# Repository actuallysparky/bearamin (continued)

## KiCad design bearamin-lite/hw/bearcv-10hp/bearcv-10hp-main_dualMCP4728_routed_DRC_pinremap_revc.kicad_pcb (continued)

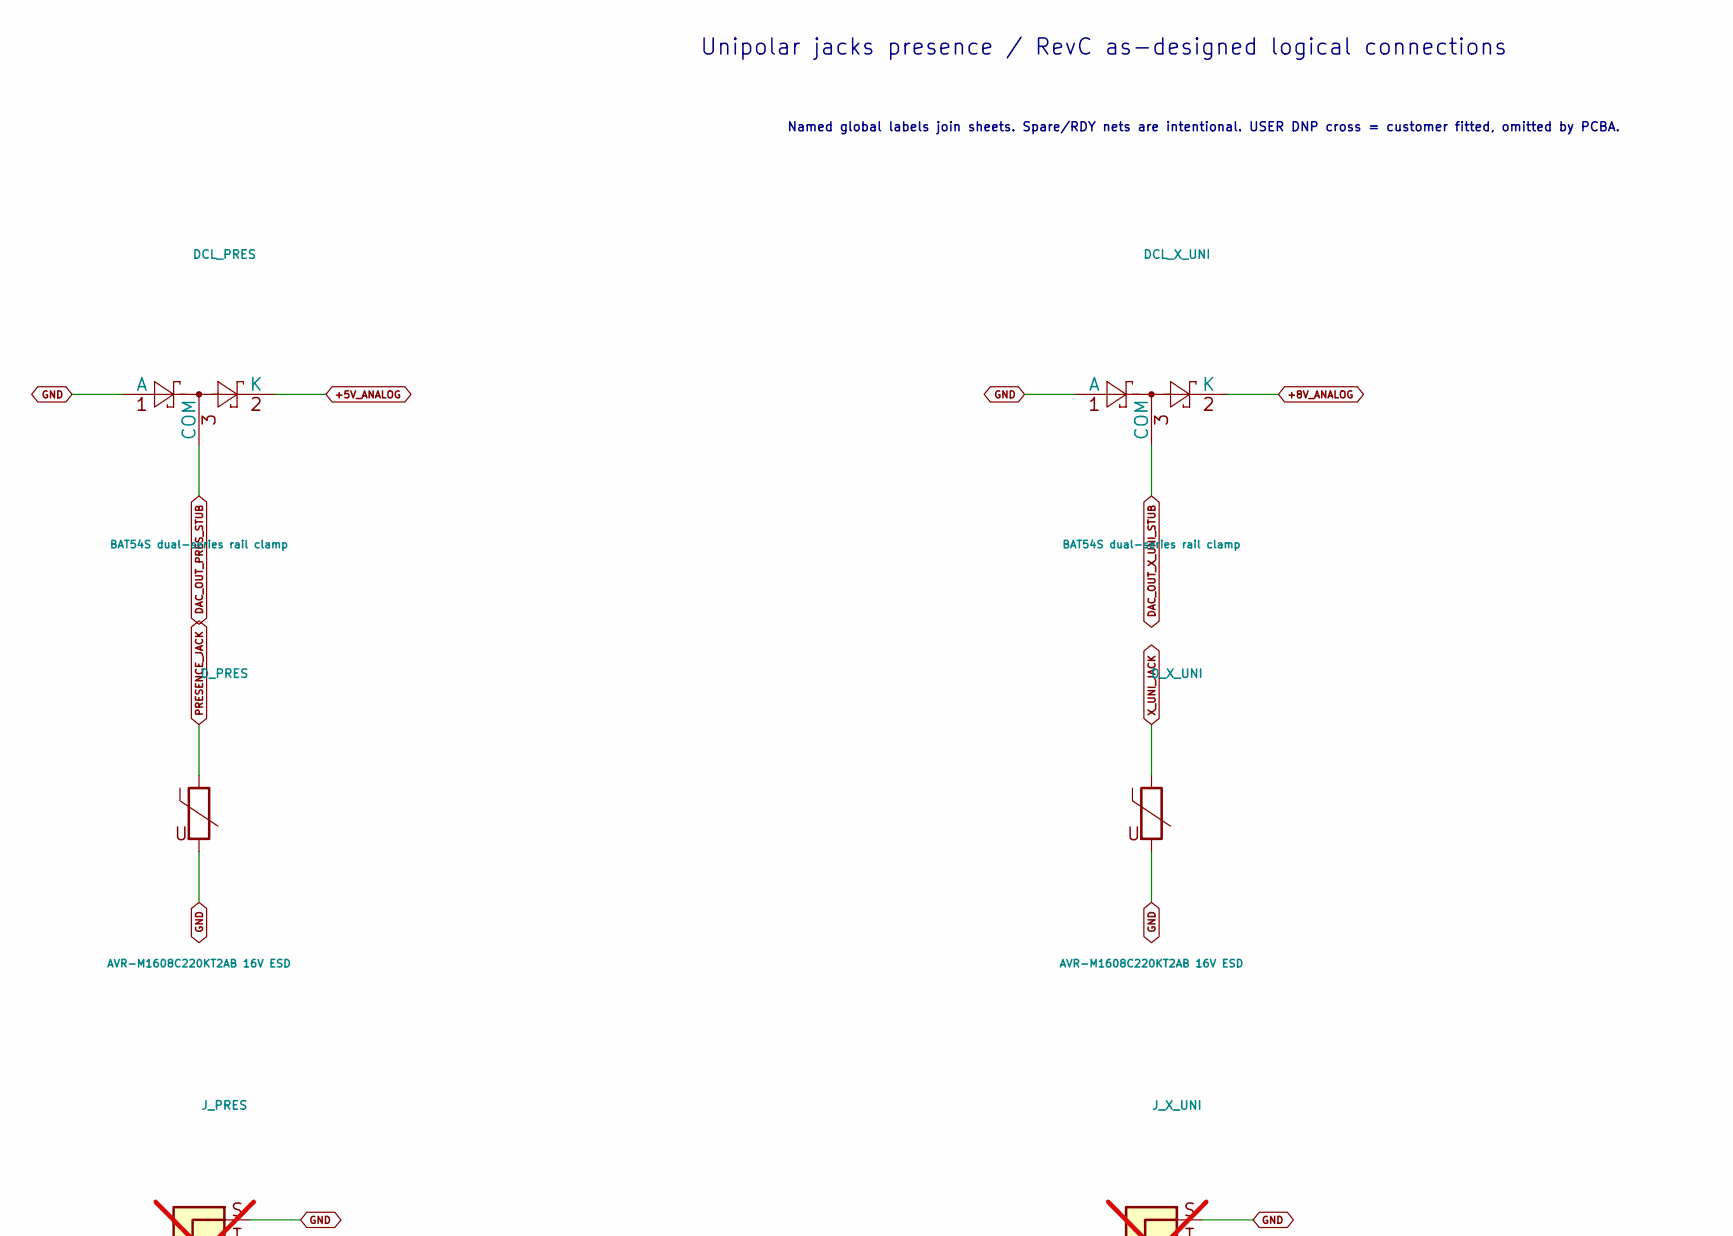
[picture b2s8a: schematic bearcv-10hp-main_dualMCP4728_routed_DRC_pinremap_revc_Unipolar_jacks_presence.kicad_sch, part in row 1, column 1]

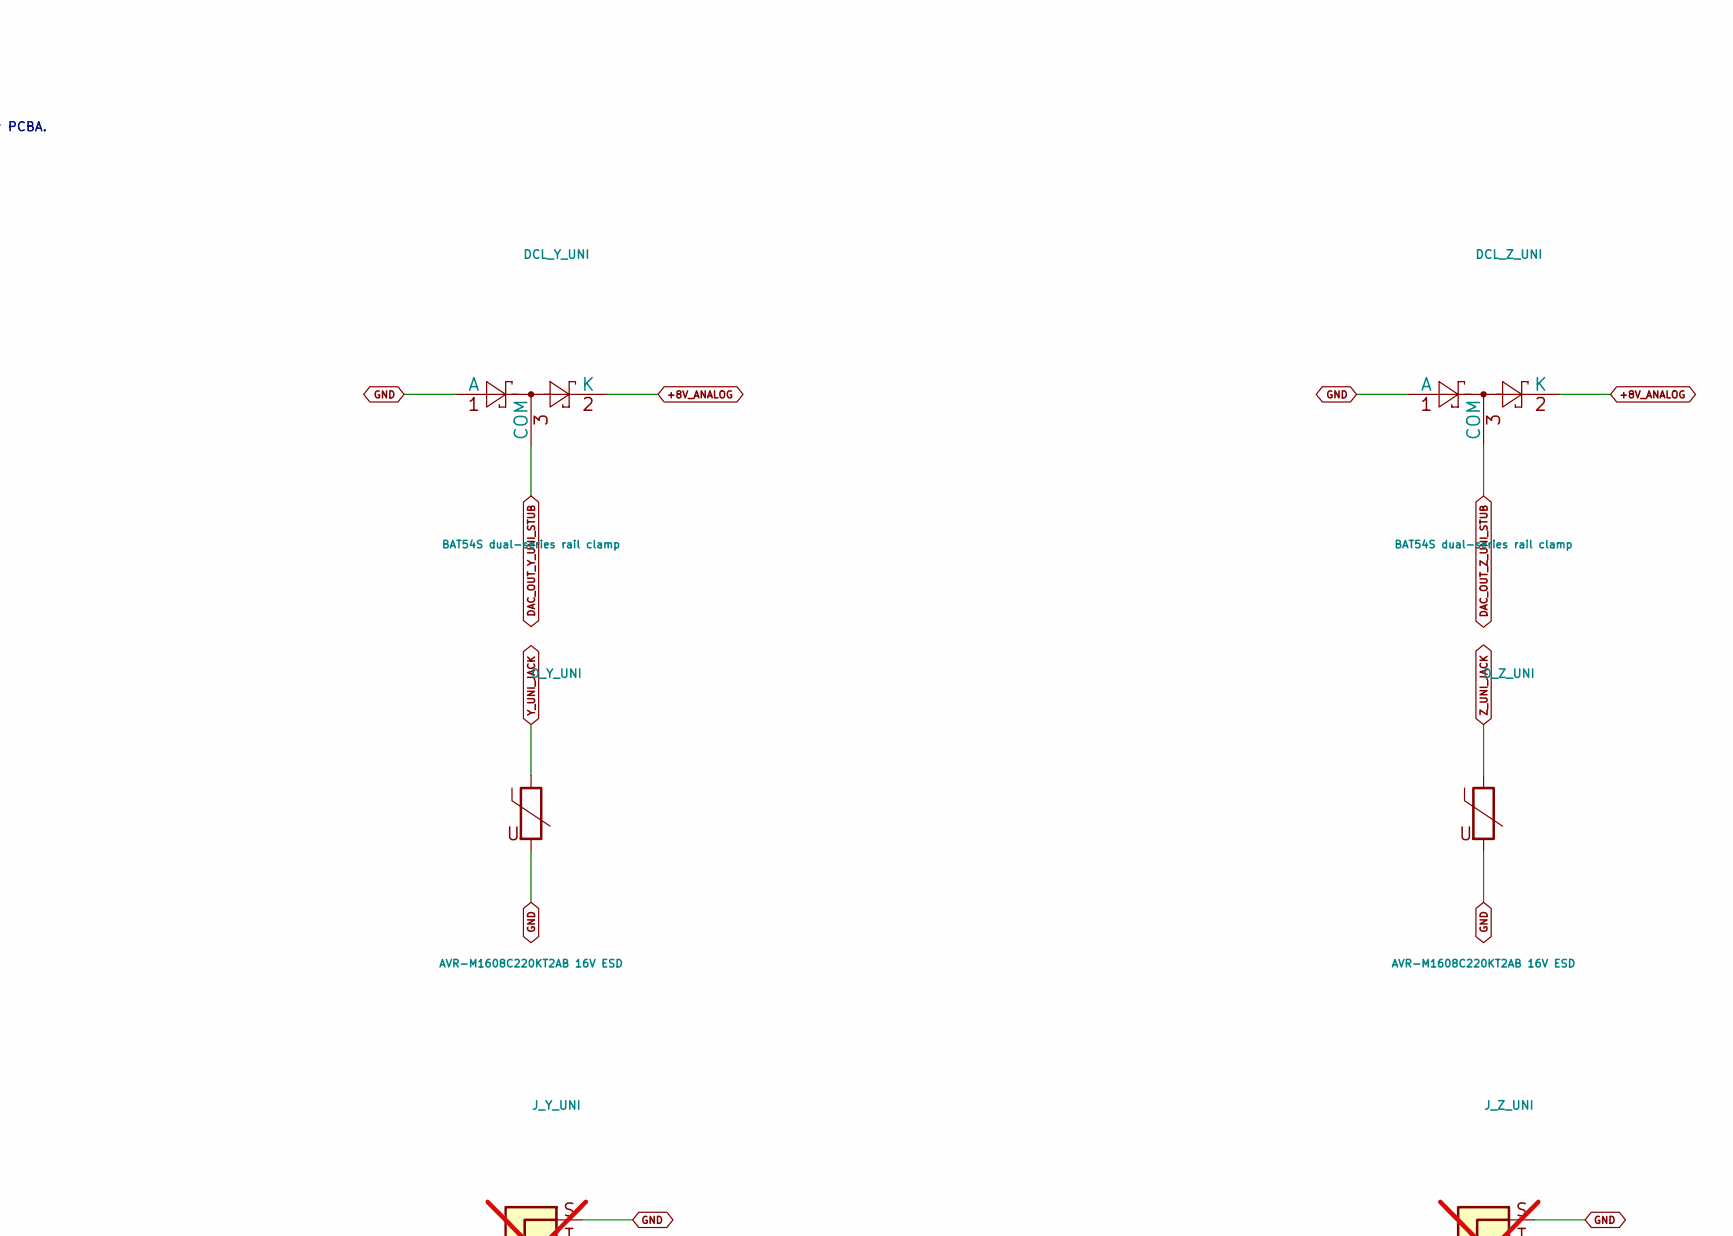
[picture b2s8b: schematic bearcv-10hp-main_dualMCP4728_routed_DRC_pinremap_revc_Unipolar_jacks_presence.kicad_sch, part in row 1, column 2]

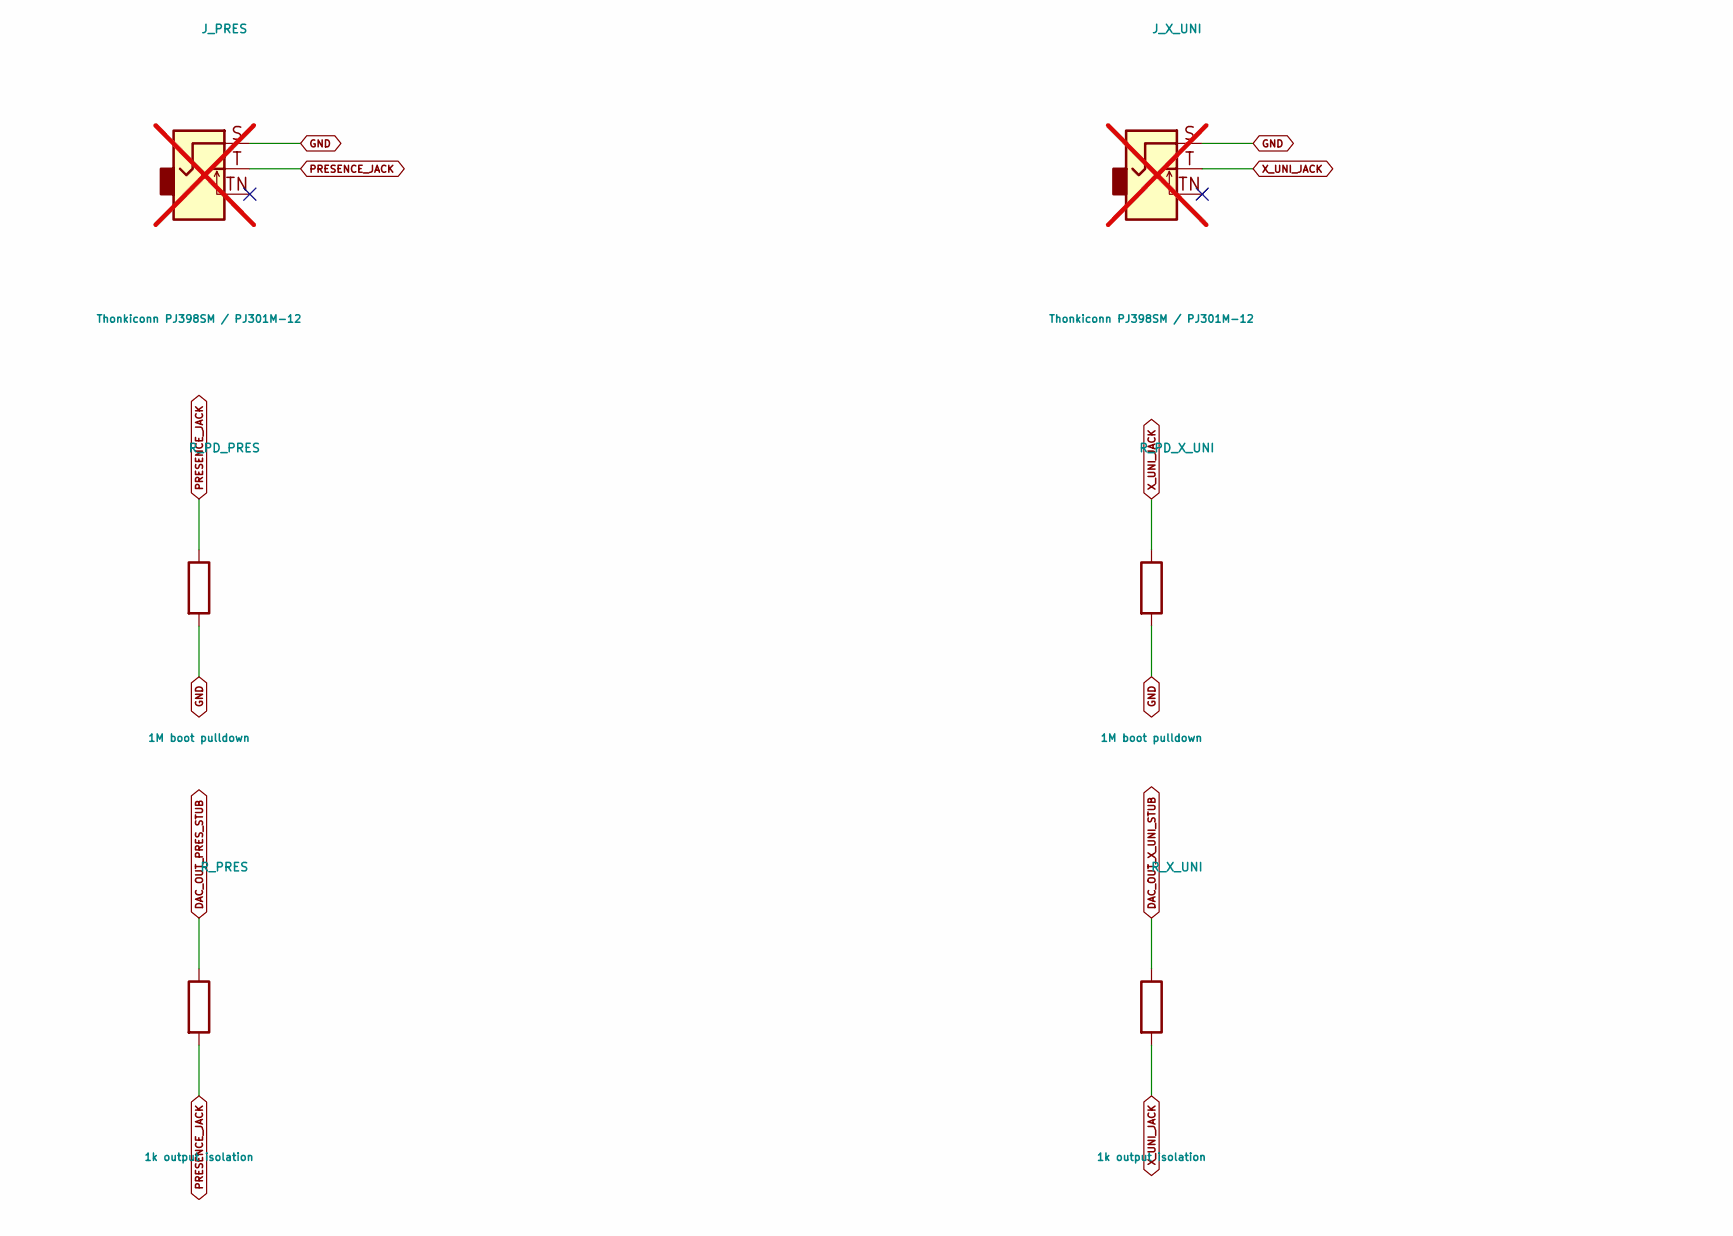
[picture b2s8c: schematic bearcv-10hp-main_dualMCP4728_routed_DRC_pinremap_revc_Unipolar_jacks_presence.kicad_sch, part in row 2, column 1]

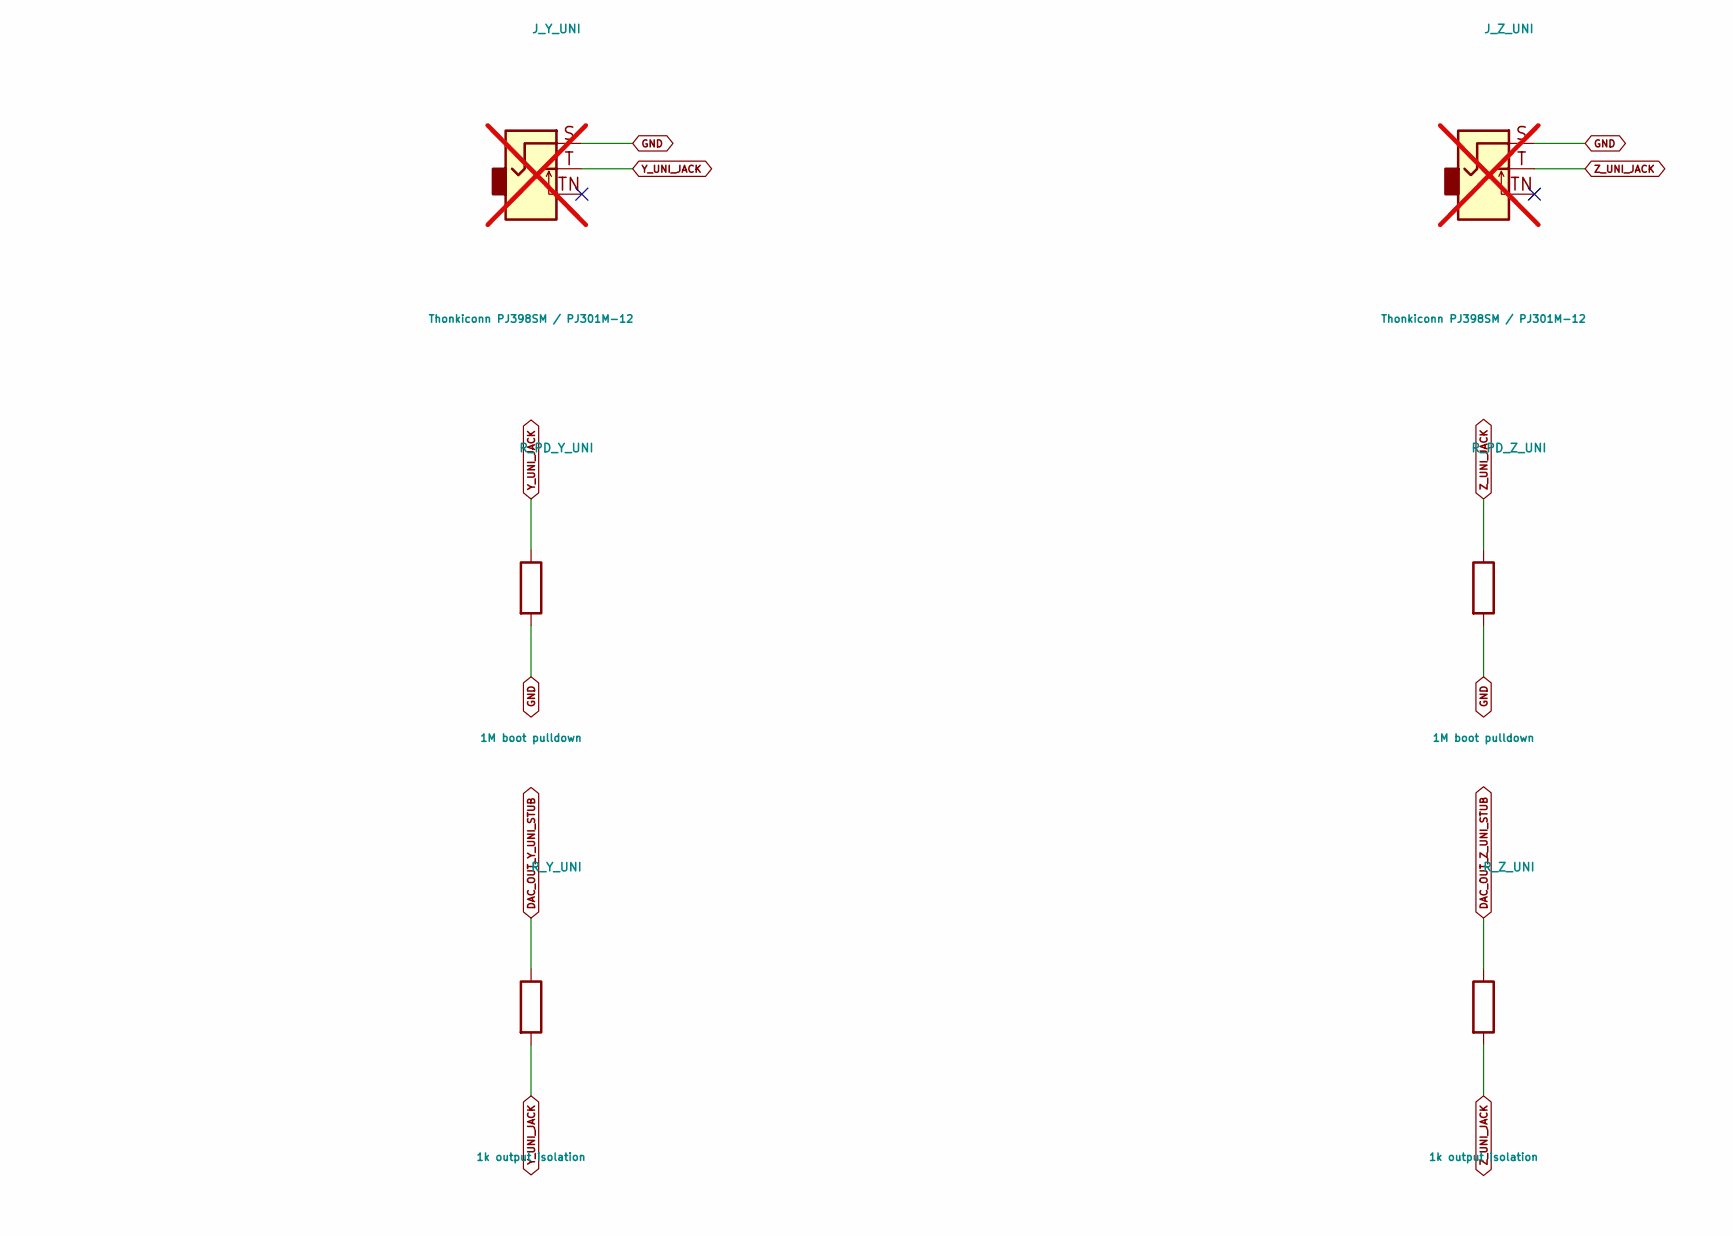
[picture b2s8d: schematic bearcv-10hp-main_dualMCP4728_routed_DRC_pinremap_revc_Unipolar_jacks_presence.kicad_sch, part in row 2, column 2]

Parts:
DCL_PRES: BAT54S dual-series rail clamp; MPN BAT54S-7-F; JLCPCB Part C83574
DCL_X_UNI: BAT54S dual-series rail clamp; MPN BAT54S-7-F; JLCPCB Part C83574
DCL_Y_UNI: BAT54S dual-series rail clamp; MPN BAT54S-7-F; JLCPCB Part C83574
DCL_Z_UNI: BAT54S dual-series rail clamp; MPN BAT54S-7-F; JLCPCB Part C83574
D_PRES: AVR-M1608C220KT2AB 16V ESD; MPN AVR-M1608C220KT2AB; JLCPCB Library Extended
D_X_UNI: AVR-M1608C220KT2AB 16V ESD; MPN AVR-M1608C220KT2AB; JLCPCB Library Extended
D_Y_UNI: AVR-M1608C220KT2AB 16V ESD; MPN AVR-M1608C220KT2AB; JLCPCB Library Extended
D_Z_UNI: AVR-M1608C220KT2AB 16V ESD; MPN AVR-M1608C220KT2AB; JLCPCB Library Extended
J_PRES: Thonkiconn PJ398SM / PJ301M-12; Jack_3.5mm_QingPu_WQP-PJ398SM_Vertical_CircularHoles; MPN DNP; not fitted
J_X_UNI: Thonkiconn PJ398SM / PJ301M-12; Jack_3.5mm_QingPu_WQP-PJ398SM_Vertical_CircularHoles; MPN DNP; not fitted
J_Y_UNI: Thonkiconn PJ398SM / PJ301M-12; Jack_3.5mm_QingPu_WQP-PJ398SM_Vertical_CircularHoles; MPN DNP; not fitted
J_Z_UNI: Thonkiconn PJ398SM / PJ301M-12; Jack_3.5mm_QingPu_WQP-PJ398SM_Vertical_CircularHoles; MPN DNP; not fitted
R_PD_PRES: 1M boot pulldown; MPN 0603WAF1004T5E; JLCPCB Part C22935
R_PD_X_UNI: 1M boot pulldown; MPN 0603WAF1004T5E; JLCPCB Part C22935
R_PD_Y_UNI: 1M boot pulldown; MPN 0603WAF1004T5E; JLCPCB Part C22935
R_PD_Z_UNI: 1M boot pulldown; MPN 0603WAF1004T5E; JLCPCB Part C22935
R_PRES: 1k output isolation; MPN 0603WAF1001T5E; JLCPCB Part C21190
R_X_UNI: 1k output isolation; MPN 0603WAF1001T5E; JLCPCB Part C21190
R_Y_UNI: 1k output isolation; MPN 0603WAF1001T5E; JLCPCB Part C21190
R_Z_UNI: 1k output isolation; MPN 0603WAF1001T5E; JLCPCB Part C21190

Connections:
+5V_ANALOG: DCL_PRES.2 (K); also elsewhere on the board
+8V_ANALOG: DCL_X_UNI.2 (K), DCL_Y_UNI.2 (K), DCL_Z_UNI.2 (K); also elsewhere on the board
DAC_OUT_PRES_STUB: DCL_PRES.3 (COM), R_PRES.1; also elsewhere on the board
DAC_OUT_X_UNI_STUB: DCL_X_UNI.3 (COM), R_X_UNI.1; also elsewhere on the board
DAC_OUT_Y_UNI_STUB: DCL_Y_UNI.3 (COM), R_Y_UNI.1; also elsewhere on the board
DAC_OUT_Z_UNI_STUB: DCL_Z_UNI.3 (COM), R_Z_UNI.1; also elsewhere on the board
GND: DCL_PRES.1 (A), DCL_X_UNI.1 (A), DCL_Y_UNI.1 (A), DCL_Z_UNI.1 (A), D_PRES.2, D_X_UNI.2, D_Y_UNI.2, D_Z_UNI.2, J_PRES.S, J_X_UNI.S, J_Y_UNI.S, J_Z_UNI.S, R_PD_PRES.2, R_PD_X_UNI.2, R_PD_Y_UNI.2, R_PD_Z_UNI.2; also elsewhere on the board
PRESENCE_JACK: D_PRES.1, J_PRES.T, R_PD_PRES.1, R_PRES.2
X_UNI_JACK: D_X_UNI.1, J_X_UNI.T, R_PD_X_UNI.1, R_X_UNI.2
Y_UNI_JACK: D_Y_UNI.1, J_Y_UNI.T, R_PD_Y_UNI.1, R_Y_UNI.2
Z_UNI_JACK: D_Z_UNI.1, J_Z_UNI.T, R_PD_Z_UNI.1, R_Z_UNI.2

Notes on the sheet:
Unipolar jacks presence / RevC as-designed logical connections
Named global labels join sheets. Spare/RDY nets are intentional. USER DNP cross = customer fitted, omitted by PCBA.

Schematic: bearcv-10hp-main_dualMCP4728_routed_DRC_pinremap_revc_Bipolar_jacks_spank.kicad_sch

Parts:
DCL_SPANK: BAT54S dual-series rail clamp; MPN BAT54S-7-F; JLCPCB Part C83574
DCL_X_BI: BAT54S dual-series rail clamp; MPN BAT54S-7-F; JLCPCB Part C83574
DCL_Y_BI: BAT54S dual-series rail clamp; MPN BAT54S-7-F; JLCPCB Part C83574
DCL_Z_BI: BAT54S dual-series rail clamp; MPN BAT54S-7-F; JLCPCB Part C83574
D_SPANK: AVR-M1608C220KT2AB 16V ESD; MPN AVR-M1608C220KT2AB; JLCPCB Library Extended
D_X_BI: AVR-M1608C220KT2AB 16V ESD; MPN AVR-M1608C220KT2AB; JLCPCB Library Extended
D_Y_BI: AVR-M1608C220KT2AB 16V ESD; MPN AVR-M1608C220KT2AB; JLCPCB Library Extended
D_Z_BI: AVR-M1608C220KT2AB 16V ESD; MPN AVR-M1608C220KT2AB; JLCPCB Library Extended
J_SPANK: Thonkiconn PJ398SM / PJ301M-12; Jack_3.5mm_QingPu_WQP-PJ398SM_Vertical_CircularHoles; MPN DNP; not fitted
J_X_BI: Thonkiconn PJ398SM / PJ301M-12; Jack_3.5mm_QingPu_WQP-PJ398SM_Vertical_CircularHoles; MPN DNP; not fitted
J_Y_BI: Thonkiconn PJ398SM / PJ301M-12; Jack_3.5mm_QingPu_WQP-PJ398SM_Vertical_CircularHoles; MPN DNP; not fitted
J_Z_BI: Thonkiconn PJ398SM / PJ301M-12; Jack_3.5mm_QingPu_WQP-PJ398SM_Vertical_CircularHoles; MPN DNP; not fitted
R_PD_SPANK: 1M boot pulldown; MPN 0603WAF1004T5E; JLCPCB Part C22935
R_PD_X_BI: 1M boot pulldown; MPN 0603WAF1004T5E; JLCPCB Part C22935
R_PD_Y_BI: 1M boot pulldown; MPN 0603WAF1004T5E; JLCPCB Part C22935
R_PD_Z_BI: 1M boot pulldown; MPN 0603WAF1004T5E; JLCPCB Part C22935
R_SPANK: 1k output isolation; MPN 0603WAF1001T5E; JLCPCB Part C21190
R_X_BI: 1k output isolation; MPN 0603WAF1001T5E; JLCPCB Part C21190
R_Y_BI: 1k output isolation; MPN 0603WAF1001T5E; JLCPCB Part C21190
R_Z_BI: 1k output isolation; MPN 0603WAF1001T5E; JLCPCB Part C21190

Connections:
+5V_ANALOG: DCL_SPANK.2 (K); also elsewhere on the board
+8V_ANALOG: DCL_X_BI.2 (K), DCL_Y_BI.2 (K), DCL_Z_BI.2 (K); also elsewhere on the board
-8V_ANALOG: DCL_X_BI.1 (A), DCL_Y_BI.1 (A), DCL_Z_BI.1 (A); also elsewhere on the board
DAC_OUT_SPANK_STUB: DCL_SPANK.3 (COM), R_SPANK.1; also elsewhere on the board
DAC_OUT_X_BI_STUB: DCL_X_BI.3 (COM), R_X_BI.1; also elsewhere on the board
DAC_OUT_Y_BI_STUB: DCL_Y_BI.3 (COM), R_Y_BI.1; also elsewhere on the board
DAC_OUT_Z_BI_STUB: DCL_Z_BI.3 (COM), R_Z_BI.1; also elsewhere on the board
GND: DCL_SPANK.1 (A), D_SPANK.2, D_X_BI.2, D_Y_BI.2, D_Z_BI.2, J_SPANK.S, J_X_BI.S, J_Y_BI.S, J_Z_BI.S, R_PD_SPANK.2, R_PD_X_BI.2, R_PD_Y_BI.2, R_PD_Z_BI.2; also elsewhere on the board
SPANK_HOLD_JACK: D_SPANK.1, J_SPANK.T, R_PD_SPANK.1, R_SPANK.2
X_BI_JACK: D_X_BI.1, J_X_BI.T, R_PD_X_BI.1, R_X_BI.2
Y_BI_JACK: D_Y_BI.1, J_Y_BI.T, R_PD_Y_BI.1, R_Y_BI.2
Z_BI_JACK: D_Z_BI.1, J_Z_BI.T, R_PD_Z_BI.1, R_Z_BI.2

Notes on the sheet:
Bipolar jacks spank / RevC as-designed logical connections
Named global labels join sheets. Spare/RDY nets are intentional. USER DNP cross = customer fitted, omitted by PCBA.

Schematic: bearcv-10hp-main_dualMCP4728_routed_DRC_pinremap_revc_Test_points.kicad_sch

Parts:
TP_3V3: 3V3; MPN N/A
TP_5A: 5A; MPN N/A
TP_5B: 5B; MPN N/A
TP_8N: -8; MPN N/A
TP_8P: +8; MPN N/A
TP_12N: -12; MPN N/A
TP_12P: +12; MPN N/A
TP_BIAS: BIAS; MPN N/A
TP_BRAW: BRAW; MPN N/A
TP_GND1: GND; MPN N/A
TP_LDB: LDB; MPN N/A
TP_LDU: LDU; MPN N/A
TP_SCL3: SCL3; MPN N/A
TP_SCL5: SCL5; MPN N/A
TP_SDA3: SDA3; MPN N/A
TP_SDA5: SDA5; MPN N/A
TP_URAW: URAW; MPN N/A

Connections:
+3V3_DIGITAL: TP_3V3.1; also elsewhere on the board
+5V_ANALOG: TP_5A.1; also elsewhere on the board
+5V_BUCK: TP_5B.1; also elsewhere on the board
+8V_ANALOG: TP_8P.1; also elsewhere on the board
+12V_PROT: TP_12P.1; also elsewhere on the board
-8V_ANALOG: TP_8N.1; also elsewhere on the board
-12V_PROT: TP_12N.1; also elsewhere on the board
BIP_DAC_BIAS_RAW: TP_BIAS.1; also elsewhere on the board
BIP_DAC_X_RAW: TP_BRAW.1; also elsewhere on the board
DAC_BIP_LDAC_5V: TP_LDB.1; also elsewhere on the board
DAC_I2C_SCL_3V3: TP_SCL3.1; also elsewhere on the board
DAC_I2C_SCL_5V: TP_SCL5.1; also elsewhere on the board
DAC_I2C_SDA_3V3: TP_SDA3.1; also elsewhere on the board
DAC_I2C_SDA_5V: TP_SDA5.1; also elsewhere on the board
DAC_UNI_LDAC_5V: TP_LDU.1; also elsewhere on the board
GND: TP_GND1.1; also elsewhere on the board
UNI_DAC_X_RAW: TP_URAW.1; also elsewhere on the board

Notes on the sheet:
Test points / RevC as-designed logical connections
Named global labels join sheets. Spare/RDY nets are intentional. USER DNP cross = customer fitted, omitted by PCBA.

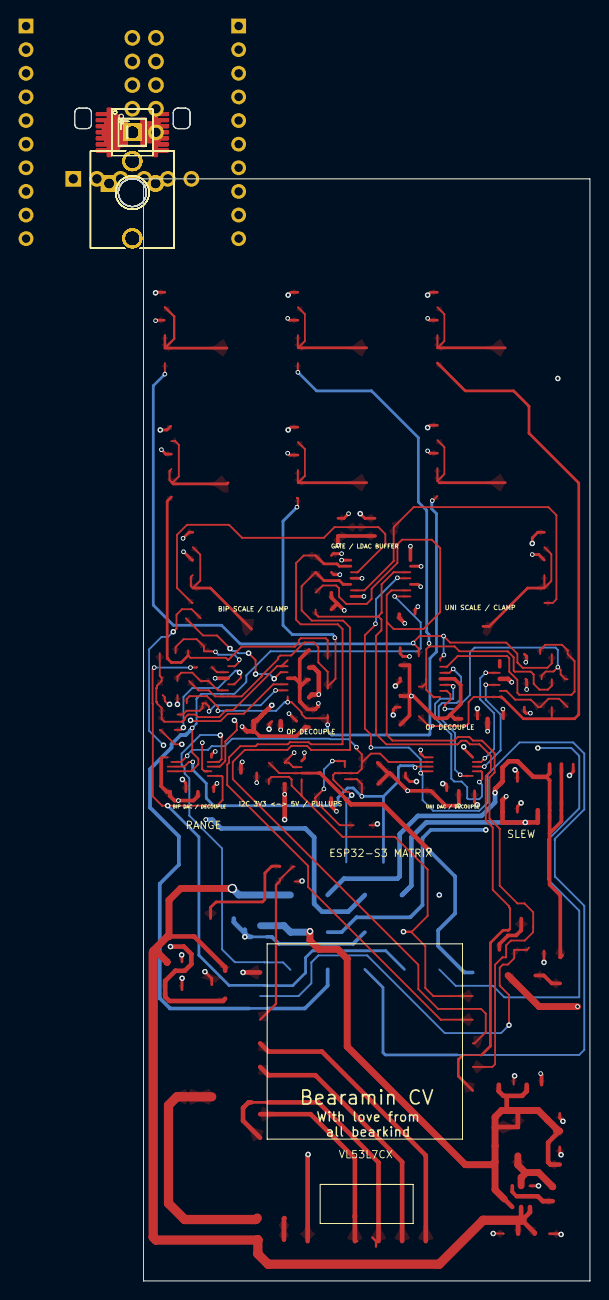
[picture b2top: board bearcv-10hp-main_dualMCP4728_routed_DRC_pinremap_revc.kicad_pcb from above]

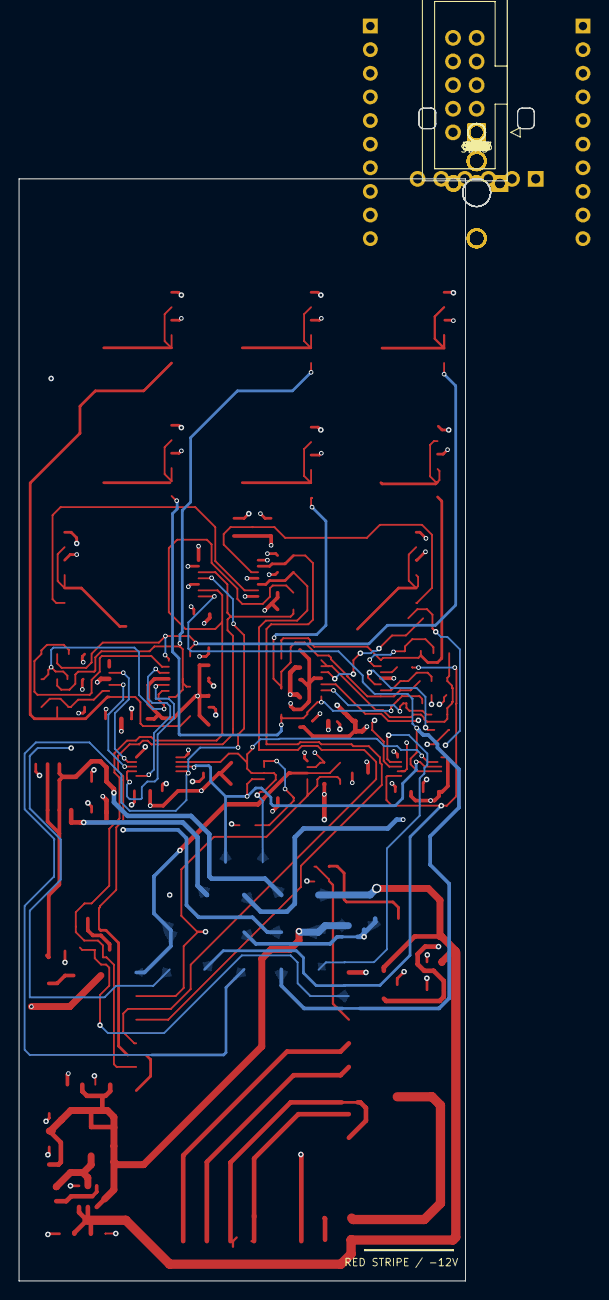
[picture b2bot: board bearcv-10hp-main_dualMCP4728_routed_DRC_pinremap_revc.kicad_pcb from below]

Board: 4 copper layers, 55.4 x 126.1 mm, 128 parts (18 on the bottom side), 69 nets.

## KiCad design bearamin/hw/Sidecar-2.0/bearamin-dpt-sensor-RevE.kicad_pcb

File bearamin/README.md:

# Bearamin

The full meal deal for droners: a specialist nerd tool with optical gesture control, five sound and CV modes, saved presets, and a browser interface for your Eurorack patch.

A VL53L7CX depth sensor and Waveshare ESP32-S3 Matrix track your hand. A XIAO Wi-Fi sidecar hosts the controls, while the [dsp.coffee DPT](https://github.com/joemisra/dpt) makes the audio, CV and gates.

## Play

CV8 selects Modal, Sympathetic Strings, Karplus-Strong, FM drone, or direct CV mode. The first three voices build on Mutable Instruments Rings. Move above the sensor to shape X/Y/Z, pitch and roll; proximity and impact gestures provide gates. The sidecar browser interface follows the physical mode selector and edits its mappings and sound controls.

Your boot default is saved in MatrixCore. Named presets use the sidecar SD card.

## Sources

- `firmware/`: MatrixCore, XIAO sidecar, shared protocols and supporting target variants.
- `dpt/DPT.multimode/`: Bearamin's DPT application.
- `hw/`: current sidecar, sensor-expander and panel designs.
- `third_party/`: Bearfield processing and licensed Rings/stmlib source.

These are beta releases. AMOLED is deprecated and is excluded from this publication. The Rev E sidecar PCB currently uses its Rev D connectivity sheet.

See [development](DEVELOPMENT.md) and [wiring](WIRING.md) before building. The DPT application requires the external DPT platform, libDaisy, DaisySP and an ARM embedded toolchain. ESP32 targets use Arduino ESP32 3.3.11.

[Family, credits and licensing](../README.md)

## Build

Run `./setup-dpt.sh`, then `./build.sh --all` from this folder. Run `./test.sh` for the host contracts. The bootstrap pins the DPT and libDaisy revisions and applies the included boot/SD patches. Build output stays in `_local/`; provide your own network configuration for the sidecar.

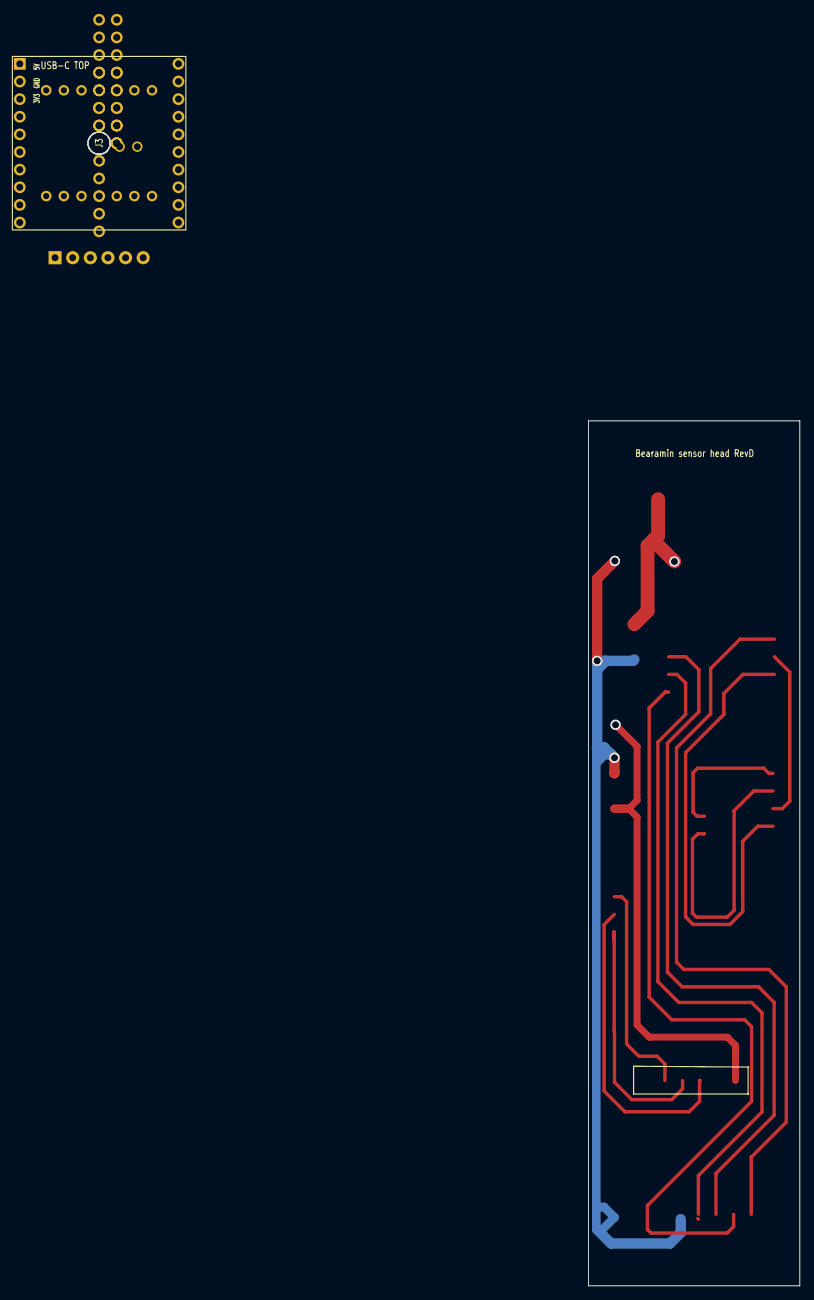
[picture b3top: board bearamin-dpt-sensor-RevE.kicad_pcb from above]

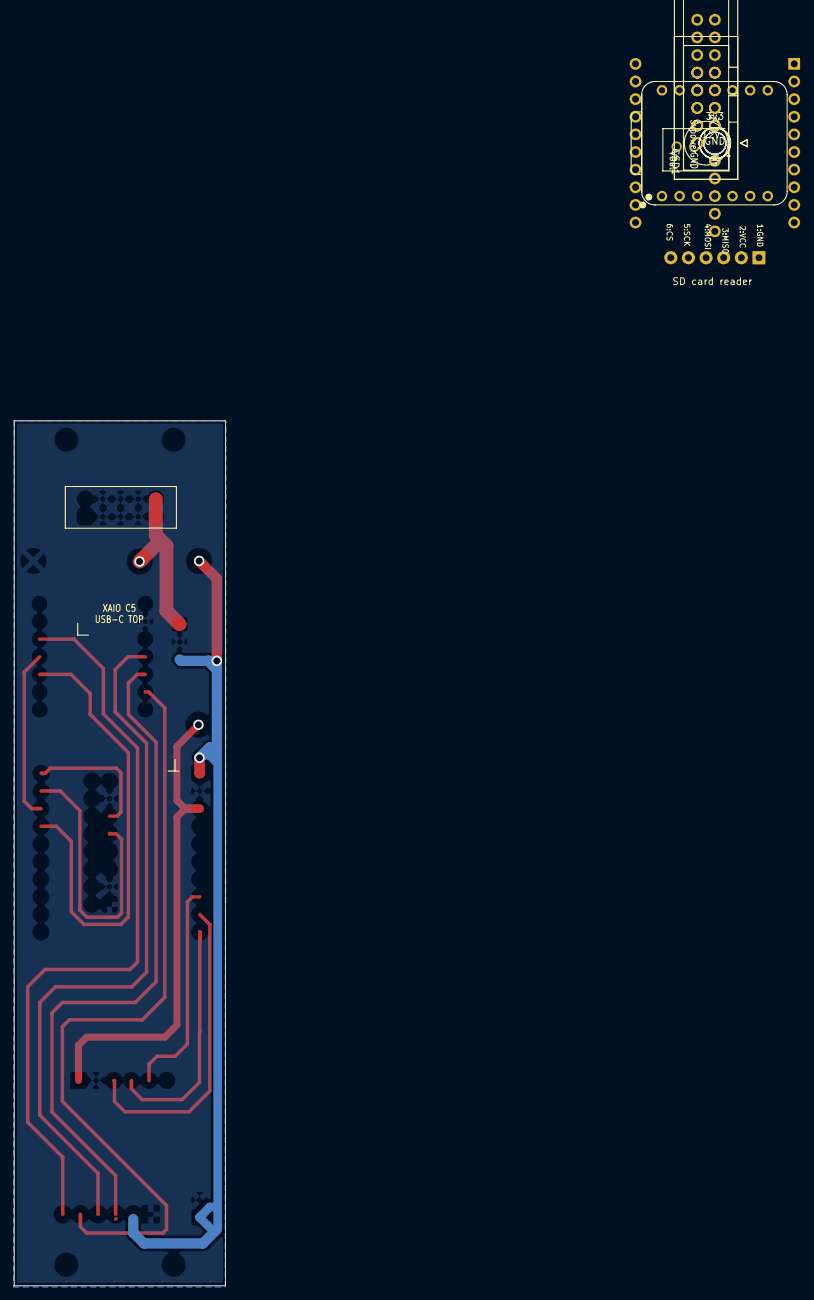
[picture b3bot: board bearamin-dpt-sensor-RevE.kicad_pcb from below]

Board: 2 copper layers, 30.4 x 124.6 mm, 16 parts (10 on the bottom side), 15 nets.

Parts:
3v3 test: 3v3; TestPoint_Pad_D4.0mm
5v test: 5v; TestPoint_Pad_D4.0mm
5vpower: SIP3_11.6x8.5mm
12v test: 12v; TestPoint_Pad_D4.0mm
CSD1: 47uF 10V; CP_Radial_D6.3mm_P2.50mm
DPTConnector: IDC-Header_2x08_P2.54mm_Vertical
Europlug: Eurorack power; IDC-Header_2x05_P2.54mm_Vertical
H1, H2, H3, H4: MountingHole_3.2mm_M3
J3: VL53L7CX_8x8_Header
JSD1: Micro SD Card Adapter (user-supplied); MicroSD_SPI_Module_6Pin_24x42mm
TND test: GND; TestPoint_Pad_D4.0mm
U1: Seeed XIAO ESP32-S3; XIAO-ESP32-S3-DIP
U3: Waveshare ESP32-S3-Matrix; Waveshare_ESP32-S3-Matrix

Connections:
+3V3: 3v3 test.3v3, J3.1, U3.3V3
+5V: 5v test.5v, 5vpower.3, CSD1.1, JSD1.2, U1.14, U3.5V
+12V_RACK: 5vpower.1, 12v test.12v, Europlug.9, Europlug.10
BEARAMIN_TX_D6_GPIO43_TO_DPT_RX: DPTConnector.11, U3.GP33
DPT_TX_TO_BEARAMIN_RX_D7_GPIO44: DPTConnector.9, U3.GP34
GND: 5vpower.2, CSD1.2, DPTConnector.1, DPTConnector.3, DPTConnector.13, Europlug.3, Europlug.4, Europlug.5, Europlug.6, Europlug.7, Europlug.8, J3.2, JSD1.1, TND test.GND, U1.13, U3.GND
MATRIX_SCL_D1_GPIO2: J3.3, U3.GP2
MATRIX_SDA_D0_GPIO1: J3.4, U3.GP1
MATRIX_TX_GPIO35_TO_XIAO_RX_D3_GPIO4: U1.4, U3.GP35
SD_CS_D2_GPIO3: JSD1.6, U1.3
SD_MISO_D9_GPIO8: JSD1.3, U1.10
SD_MOSI_D10_GPIO9: JSD1.4, U1.11
SD_SCK_D8_GPIO7: JSD1.5, U1.9
VL53L7CX_LPR_GPIO3: J3.5, U3.GP3
XIAO_TX_D4_GPIO5_TO_MATRIX_RX_GPIO36: U1.5, U3.GP36

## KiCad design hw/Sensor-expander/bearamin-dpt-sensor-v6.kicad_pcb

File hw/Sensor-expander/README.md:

# Bearamin Sensor Expander

The canonical publication hardware is the v6 sidecar board:

- `bearamin-dpt-sensor-v6.kicad_pro`
- `bearamin-dpt-sensor-v6.kicad_pcb`

The PCB contains the XIAO ESP32-S3 Wi-Fi sidecar, ESP32-S3 MatrixCore,
VL53L7CX 8x8 sensor connection, DPT link, and power components. It has no
retired single-point sensor footprint or connection.

The current board is routed and KiCad reports no unconnected pads. Its current
DRC report contains 14 warnings for local footprint overrides and silkscreen
size/overlap, so review and resolve those items before fabrication.

The v6 release is board-authoritative and does not attach the older v5
schematic. The v5 board, its schematic, earlier revisions, autorouter
intermediates, and generated fabrication exports remain local design history
and are not part of the publication bundle.

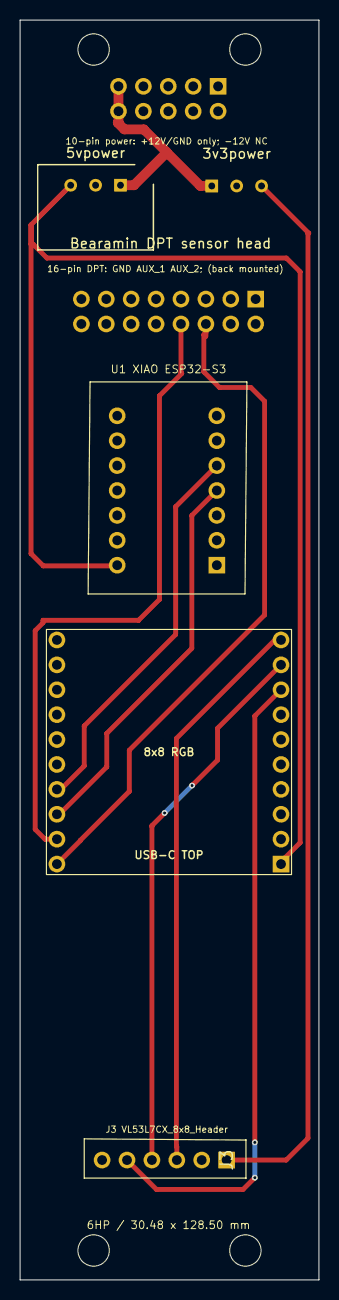
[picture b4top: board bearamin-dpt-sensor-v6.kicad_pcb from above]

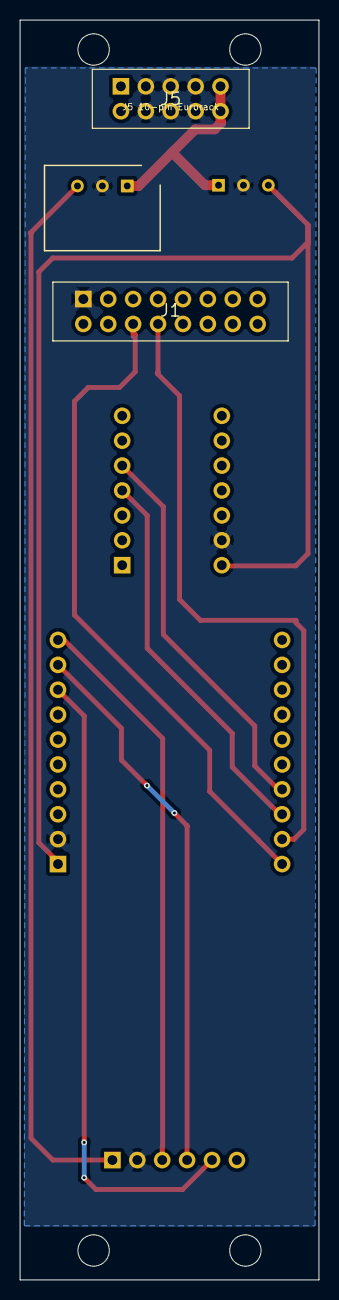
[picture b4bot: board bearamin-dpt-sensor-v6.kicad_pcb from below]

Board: 2 copper layers, 30.5 x 128.5 mm, 11 parts (3 on the bottom side), 11 nets.

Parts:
3v3power, 5vpower: SIP3_11.6x8.5mm
H1, H2, H3, H4: MountingHole_3.2mm_M3
J1: 16-pin DPT EXP link; DPT_Link_2x8_IDC
J3: VL53L7CX_8x8_Header
J5: 10-pin Eurorack power; Eurorack_Power_2x5_IDC
U1: Seeed XIAO ESP32-S3; Seeed_XIAO_ESP32S3_Header
U3: Waveshare ESP32-S3-Matrix; Waveshare_ESP32-S3-Matrix

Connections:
+3V3: 3v3power.3, J3.1
+5V: 5vpower.3, U1.14, U3.5V
+12V_RACK: 3v3power.1, 5vpower.1, J5.9, J5.10
BEARAMIN_TX_D6_GPIO43_TO_DPT_RX: J1.6, U3.GP33
DPT_TX_TO_BEARAMIN_RX_D7_GPIO44: J1.8, U3.GP34
GND: 3v3power.2, 5vpower.2, J1.1, J3.2, J5.3, J5.4, J5.5, J5.6, J5.7, J5.8, U1.13, U3.GND
MATRIX_SCL_D1_GPIO2: J3.4, U3.GP2
MATRIX_SDA_D0_GPIO1: J3.3, U3.GP1
MATRIX_TX_GPIO35_TO_XIAO_RX_D3_GPIO4: U1.4, U3.GP35
VL53L7CX_LPR_GPIO3: J3.5, U3.GP3
XIAO_TX_D4_GPIO5_TO_MATRIX_RX_GPIO36: U1.5, U3.GP36
